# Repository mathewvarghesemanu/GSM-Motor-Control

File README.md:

# GSM Motor Control 

Refer https://learn.adafruit.com/adafruit-fona-mini-gsm-gprs-cellular-phone-module?view=all

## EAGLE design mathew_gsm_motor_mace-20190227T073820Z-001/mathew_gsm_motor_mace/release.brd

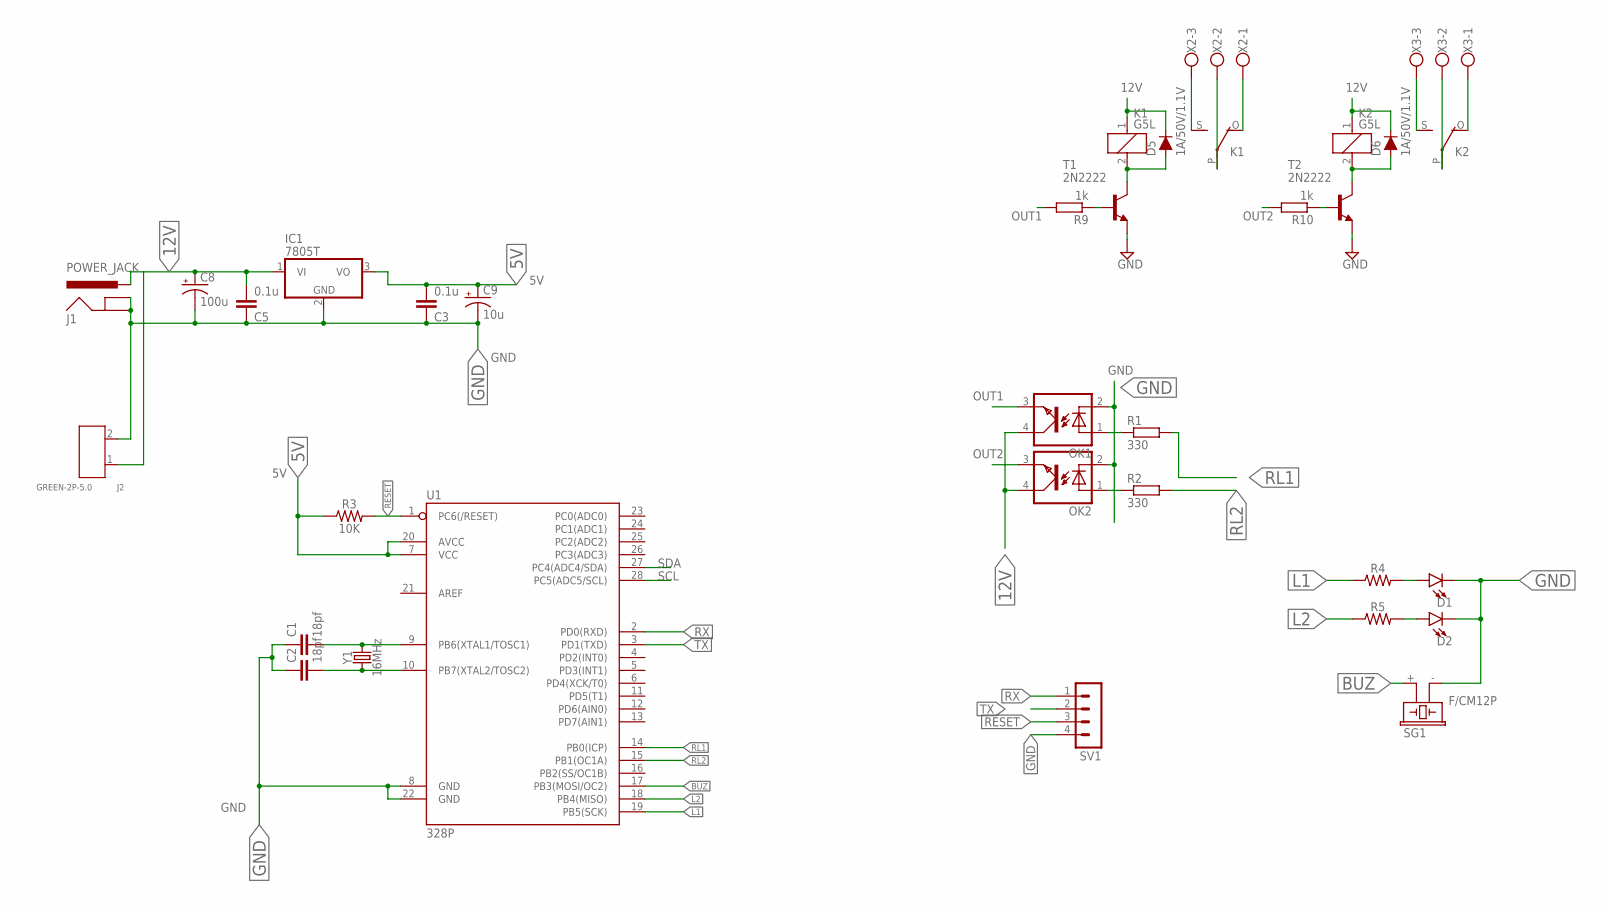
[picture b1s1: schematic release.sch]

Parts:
C1, C2: 18pf; C2.5-3
C3, C5: 0.1u; C2.5-3
C8: 100u; E2,5-7
C9: 10u; E2,5-5
D1, D2: LED5MM; LED_5MM
D5, D6: 1A/50V/1.1V; DIODE-1N4001
IC1: 7805T; TO220H
J1: POWER_JACK; POWER_JACK_PTH
J2: GREEN-2P-5.0; H2-5.0-10.5X8.0MM
K1, K2: G5L; G5LE
OK1, OK2: LTV816; DIL04
R1, R2: 330; 0207/7
R3: 10K; AXIAL-0.3
R4, R5: AXIAL-0.3
R9, R10: 1k; 0207/7
SG1: F/CM12P
SV1: MA04-1
T1, T2: 2N2222; TO92-EBC-OVAL
U1: 328P; DIP28
X2, X3: W237-103
Y1: 16MHz; HC49US

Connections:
5V: C3.2, C9.+, IC1.3 (VO), R3.P$1 (1), U1.7 (VCC), U1.20 (AVCC)
12V: C5.2, C8.+, D5.C, D6.C, IC1.1 (VI), J1.PWR, J2.1, K1.1, K2.1, OK1.4 (COL), OK2.4 (COL)
BUZ: SG1.+ (1), U1.17 (PB3(MOSI/OC2))
GND: C1.1, C2.1, C3.1, C5.1, C8.-, C9.-, D1.K (C), D2.K (C), IC1.2 (GND), J1.GND, J1.GNDBREAK, J2.2, OK1.2 (C), OK2.2 (C), SG1.- (2), SV1.4, T1.E, T2.E, U1.8 (GND), U1.22 (GND)
L1: R4.P$1 (1), U1.19 (PB5(SCK))
L2: R5.P$1 (1), U1.18 (PB4(MISO))
unnamed: C1.2, U1.9 (PB6(XTAL1/TOSC1)), Y1.2
unnamed: C2.2, U1.10 (PB7(XTAL2/TOSC2)), Y1.1
unnamed: OK1.1 (A), R1.1
unnamed: OK2.1 (A), R2.1
unnamed: R9.1, T1.B
unnamed: D1.A, R4.P$2 (2)
unnamed: D2.A, R5.P$2 (2)
unnamed: K1.S, X2.3
unnamed: K1.O, X2.1
unnamed: K1.P, X2.2
unnamed: D5.A, K1.2, T1.C
unnamed: R10.1, T2.B
unnamed: K2.S, X3.3
unnamed: K2.O, X3.1
unnamed: K2.P, X3.2
unnamed: D6.A, K2.2, T2.C
OUT1: OK1.3 (EMIT), R9.2
OUT2: OK2.3 (EMIT), R10.2
RESET: R3.P$2 (2), SV1.3, U1.1 (PC6(/RESET))
RL1: R1.2, U1.14 (PB0(ICP))
RL2: R2.2, U1.15 (PB1(OC1A))
RX: SV1.1, U1.2 (PD0(RXD))
SCL: U1.28 (PC5(ADC5/SCL))
SDA: U1.27 (PC4(ADC4/SDA))
TX: SV1.2, U1.3 (PD1(TXD))

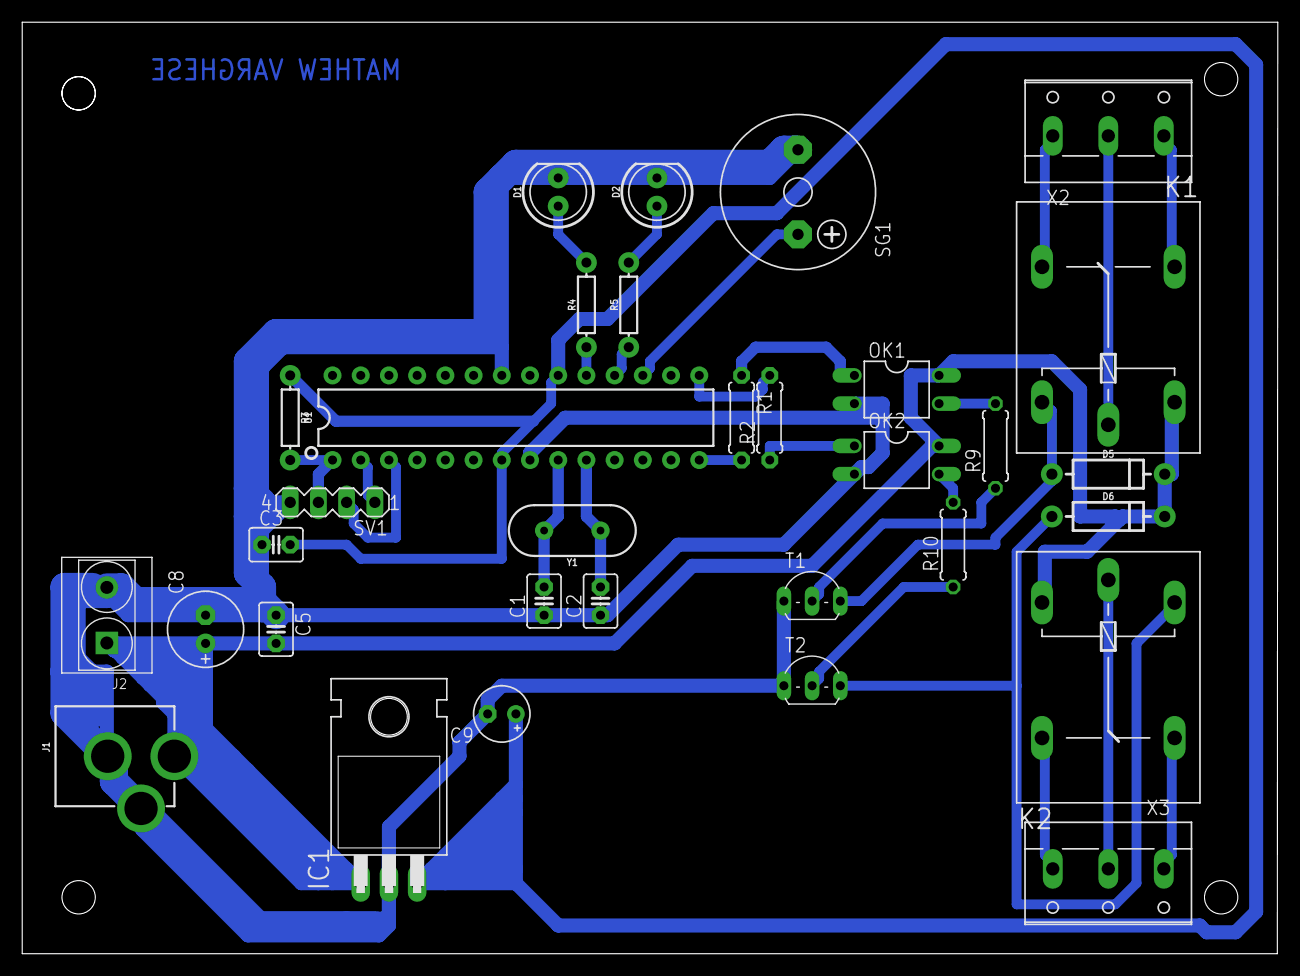
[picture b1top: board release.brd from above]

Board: 2 copper layers, 113.0 x 83.9 mm, 32 parts (0 on the bottom side), 29 nets.

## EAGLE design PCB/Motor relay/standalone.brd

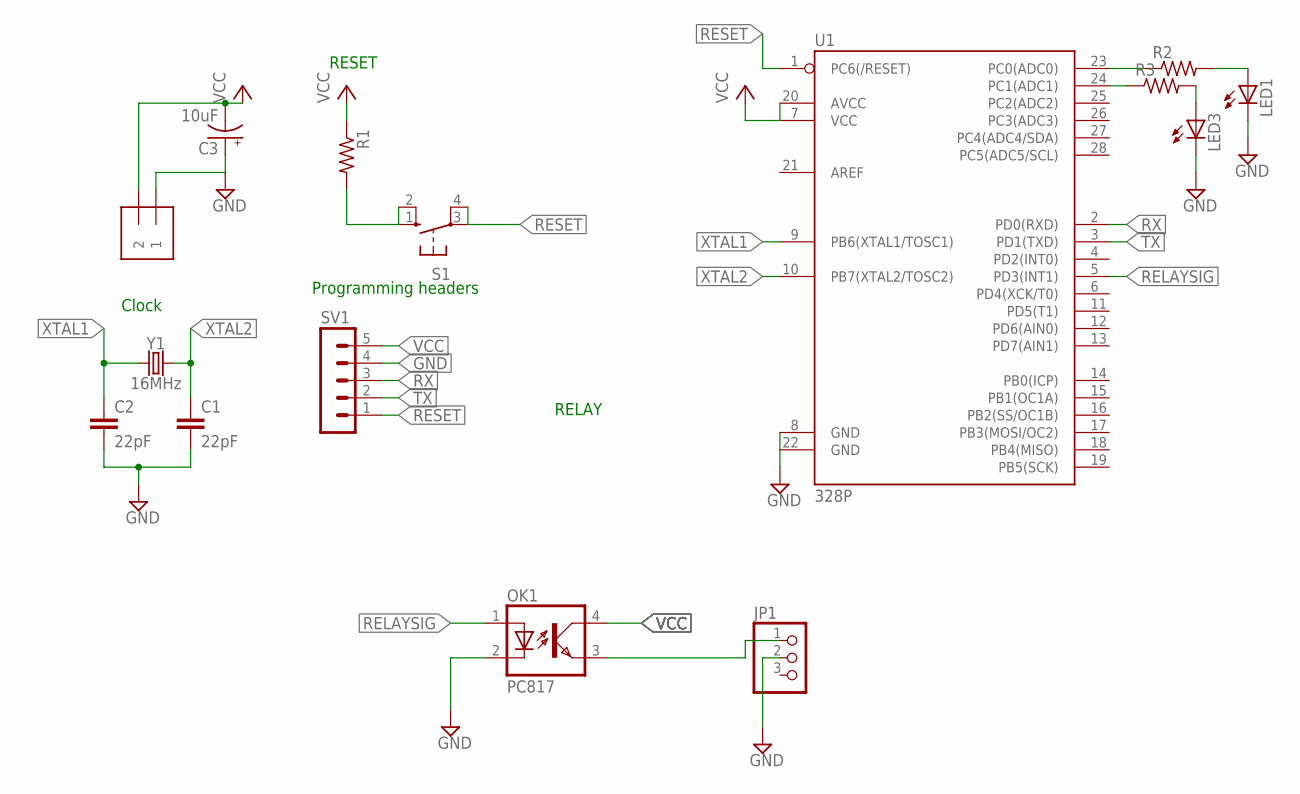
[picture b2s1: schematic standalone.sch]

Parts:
C1, C2: 22pF; CAP-PTH-2.54
C3: 10uF; CPOL-RADIAL-2.5MM-5MM
J1: 1X2-3.5MM
JP1: PINHD-1X3; 1X03
LED1, LED3: LED5MM
OK1: PC817; DIL04
R1: R-US_0617/5V; 0617V
R2: R-US_0204/5; 0204/5
R3: R-US_0204/7; 0204/7
S1: 10-XX; B3F-10XX
SV1: MA05-1
U1: 328P; DIP28
Y1: 16MHz; HC49US

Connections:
GND: C1.2, C2.2, C3.1 (+), J1.1, JP1.2, LED1.K (C), LED3.K (C), OK1.2 (C), SV1.4, U1.8 (GND), U1.22 (GND)
unnamed: LED3.A, R3.2
unnamed: JP1.1, OK1.3 (EMIT)
unnamed: R2.1, U1.23 (PC0(ADC0))
unnamed: LED1.A, R2.2
unnamed: R3.1, U1.24 (PC1(ADC1))
RELAYSIG: OK1.1 (A), U1.5 (PD3(INT1))
RESET: R1.2, S1.1 (S), S1.2 (S1), S1.3, S1.4 (P1), SV1.1, U1.1 (PC6(/RESET))
RX: SV1.3, U1.2 (PD0(RXD))
TX: SV1.2, U1.3 (PD1(TXD))
VCC: C3.2 (-), J1.2, OK1.4 (COL), R1.1, SV1.5, U1.7 (VCC), U1.20 (AVCC)
XTAL1: C2.1, U1.9 (PB6(XTAL1/TOSC1)), Y1.1
XTAL2: C1.1, U1.10 (PB7(XTAL2/TOSC2)), Y1.2

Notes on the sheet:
Clock
RESET
Programming headers
RELAY

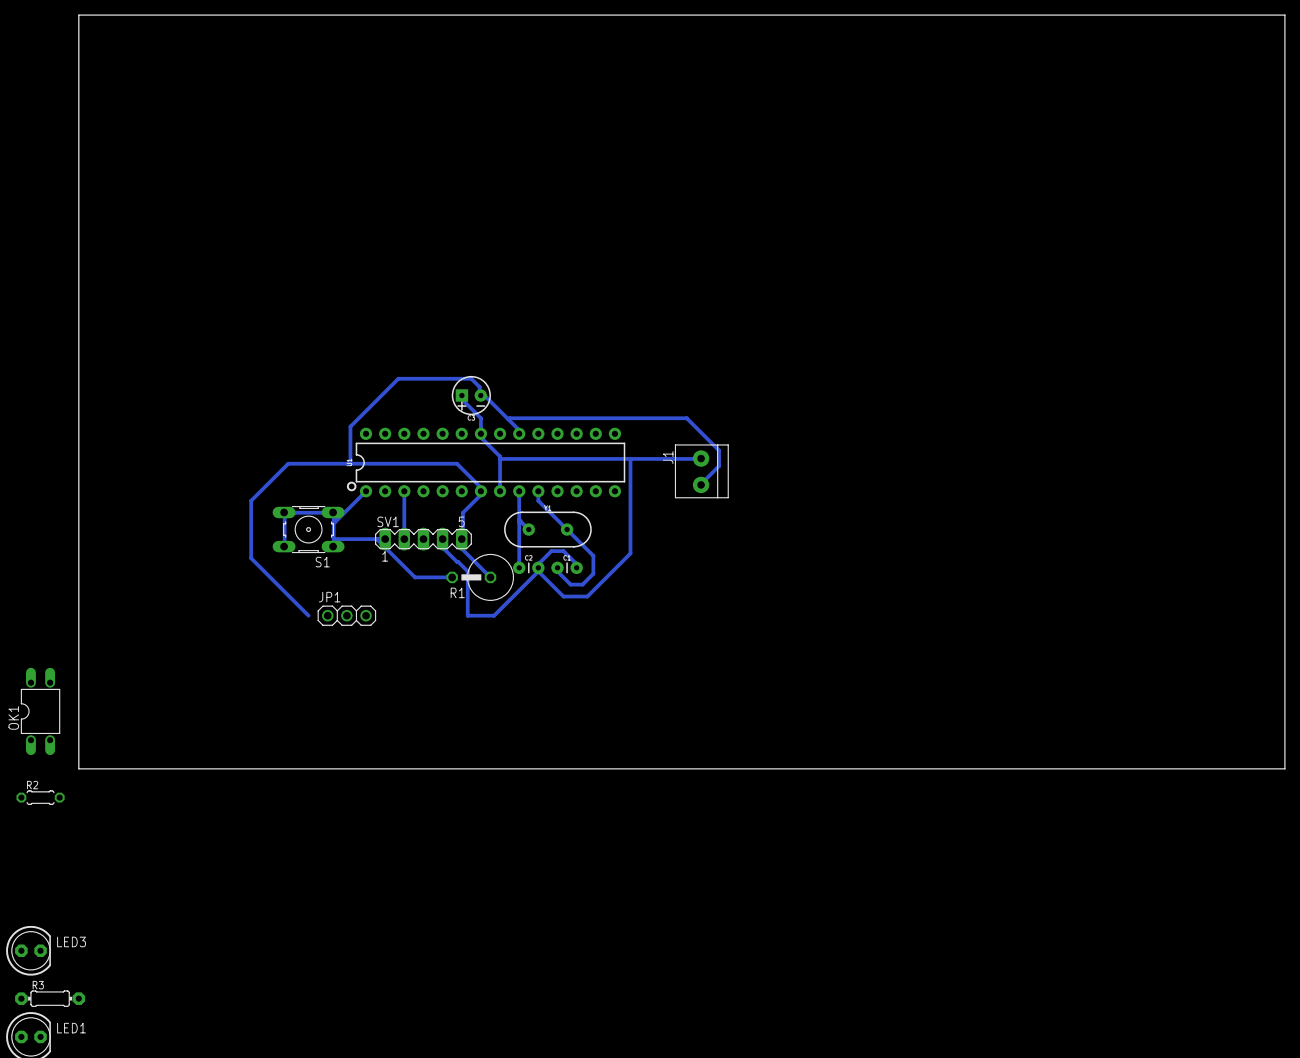
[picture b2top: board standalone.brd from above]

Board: 2 copper layers, 160.0 x 100.0 mm, 15 parts (0 on the bottom side), 13 nets.

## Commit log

2018-06-29 initial
2018-06-29 init copy
2018-07-13 extra
2018-07-14 used adafruit fona as base
2018-07-15 start1
2018-07-15 start2
2018-07-15 v3 working
2018-07-15 v4 read send
2018-07-15 replybuffer added to sms
2018-07-15 working version
2018-07-15 waiting for message implemented
2018-07-16 readme
2018-07-16 PCB init
2018-08-04 PCB MOD1
2018-08-04 MOD2
2018-08-24 Power Indicators added
2018-09-02 App added
2019-02-27 PCB arav
    PCB designed by aravind added
2019-07-11 PCB update
2020-04-25 Android app added

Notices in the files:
parts and their libraries:
SparkFun-Capacitors: Licensing: Creative Commons ShareAlike 4.0 International - https://creativecommons.org/licenses/by-sa/4.0
